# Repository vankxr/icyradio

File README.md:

# icyradio

A **S**oftware **D**efined **R**adio development board.

Initial project codename **Icy**radio originated from the device family name of the FPGA used in the [first version](https://github.com/vankxr/icyradio/tree/v1/qo100) (**ICE**40). Coincidently, the device family name of the FPGA used in this version (Artix) also resembles a very cold region, the Arctic, hence, the project codename still holds some of its sense :blush:.

## Main components
 - [XC7A100T-2FGG484](https://pt.mouser.com/datasheet/2/903/ds180_7Series_Overview-1591537.pdf) - FPGA
 - [Raspberry Pi CM4](https://datasheets.raspberrypi.com/cm4/cm4-datasheet.pdf) - Raspberry Pi Compute Module 4
 - [MT41K256M16TW-125](https://media-www.micron.com/-/media/client/global/documents/products/data-sheet/dram/ddr3/4gb_1_35v_ddr3l_xit_addendum.pdf?rev=993cd23ec9f2450c8cae38fcb35343bd) - DDR3 RAM
 - [AD9361](https://github.com/vankxr/icyradio/raw/v2/qo100/docs/ad9361_transceiver/AD9361_Datasheet_RevF.pdf) - Agile RF Transceiver
 - [SI5351C](https://www.silabs.com/documents/public/data-sheets/Si5351-B.pdf) - System clock synthesizer
 - [8V97003](https://www.renesas.com/us/en/document/dst/8v97003-datasheet?r=462341) - Frequency Synthesizer for external mixer support
 - [ADAU1372](https://www.analog.com/media/en/technical-documentation/data-sheets/ADAU1372.pdf) - Audio CODEC
 - [UPD301C](https://ww1.microchip.com/downloads/aemDocuments/documents/UNG/ProductDocuments/DataSheets/00003412A.pdf) - USB Power Delivery controller
 - [LT7182S](https://www.analog.com/media/en/technical-documentation/data-sheets/lt7182s.pdf) - Main Buck regulator

## Functional block diagram

#### v2
**Note: From v2 onwards, the only components in this repository are hardware related, no specific application software, like in v1 branches. Applications that use this hardware are kept in a separate repository (TODO: Add link)**
The goal of this project is to develop a flexible and feature rich SDR platform for tinkering. It will include, among other features, a mmWave synthesizer controlled by software to allow external mixers to be attached to the SDR and extend its frequency range (i.e. for 5G applications), and also allow interfacing to a Raspberry Pi Compute Module 4 for standalone operation.

## Dependencies
 - [vivado](https://www.xilinx.com/support/download.html) - FPGA toolchain
 - [arm-none-eabi-gcc](https://developer.arm.com/tools-and-software/open-source-software/developer-tools/gnu-toolchain/gnu-rm/downloads) - PD Controller MCU toolchain
 - [Device CMSIS](https://www.keil.com/dd2/) - CMSIS headers defining the MCU memories, peripherals, etc...
 - [Core CMSIS](https://github.com/ARM-software/CMSIS_5) - CMSIS headers defining the ARM Cores
 - [armmem](https://github.com/vankxr/armmem) - ELF file analyzer (required for the MCU Makefiles to work)
 - [SoapySDR](https://github.com/pothosware/SoapySDR) - Vendor and platform neutral SDR support library

## Software build instructions
TODO (In the meantime, check the github workflows)
### Kernel driver
TODO
### SoapySDR device driver
TODO

## Errata
 - The WP pin of the LT7182S regulator was left floating, with a placeholder resistor for pulling it up later, assuming it had an internal pulldown. Turns out it is floating, and thus it can be sampled internally as 1, write-protecting the device and forbidding configuration commands. A quick fix is to scrape a tiny bit of the ground plane near the WP resistor (R1120) pad, and shunting it to GND there with a blob of solder. The figure below exemplifies the process. The solder blob is marked in blue.

 - The FPGA INIT and DONE LED markings on the PCB are swapped (oops). In the picture below, it can be seen that D202 connects to the FPGA_DONE signal, yet it's labelled INIT. The FPGA_INIT signal connects to D201, and is labelled as DONE. It is merely an aesthetic problem, and does not affect functionality at all!

## Authors

* **João Silva** - [vankxr](https://github.com/vankxr)

## License

The content of this repository is licensed under the [GNU General Public License v3.0](LICENSE).

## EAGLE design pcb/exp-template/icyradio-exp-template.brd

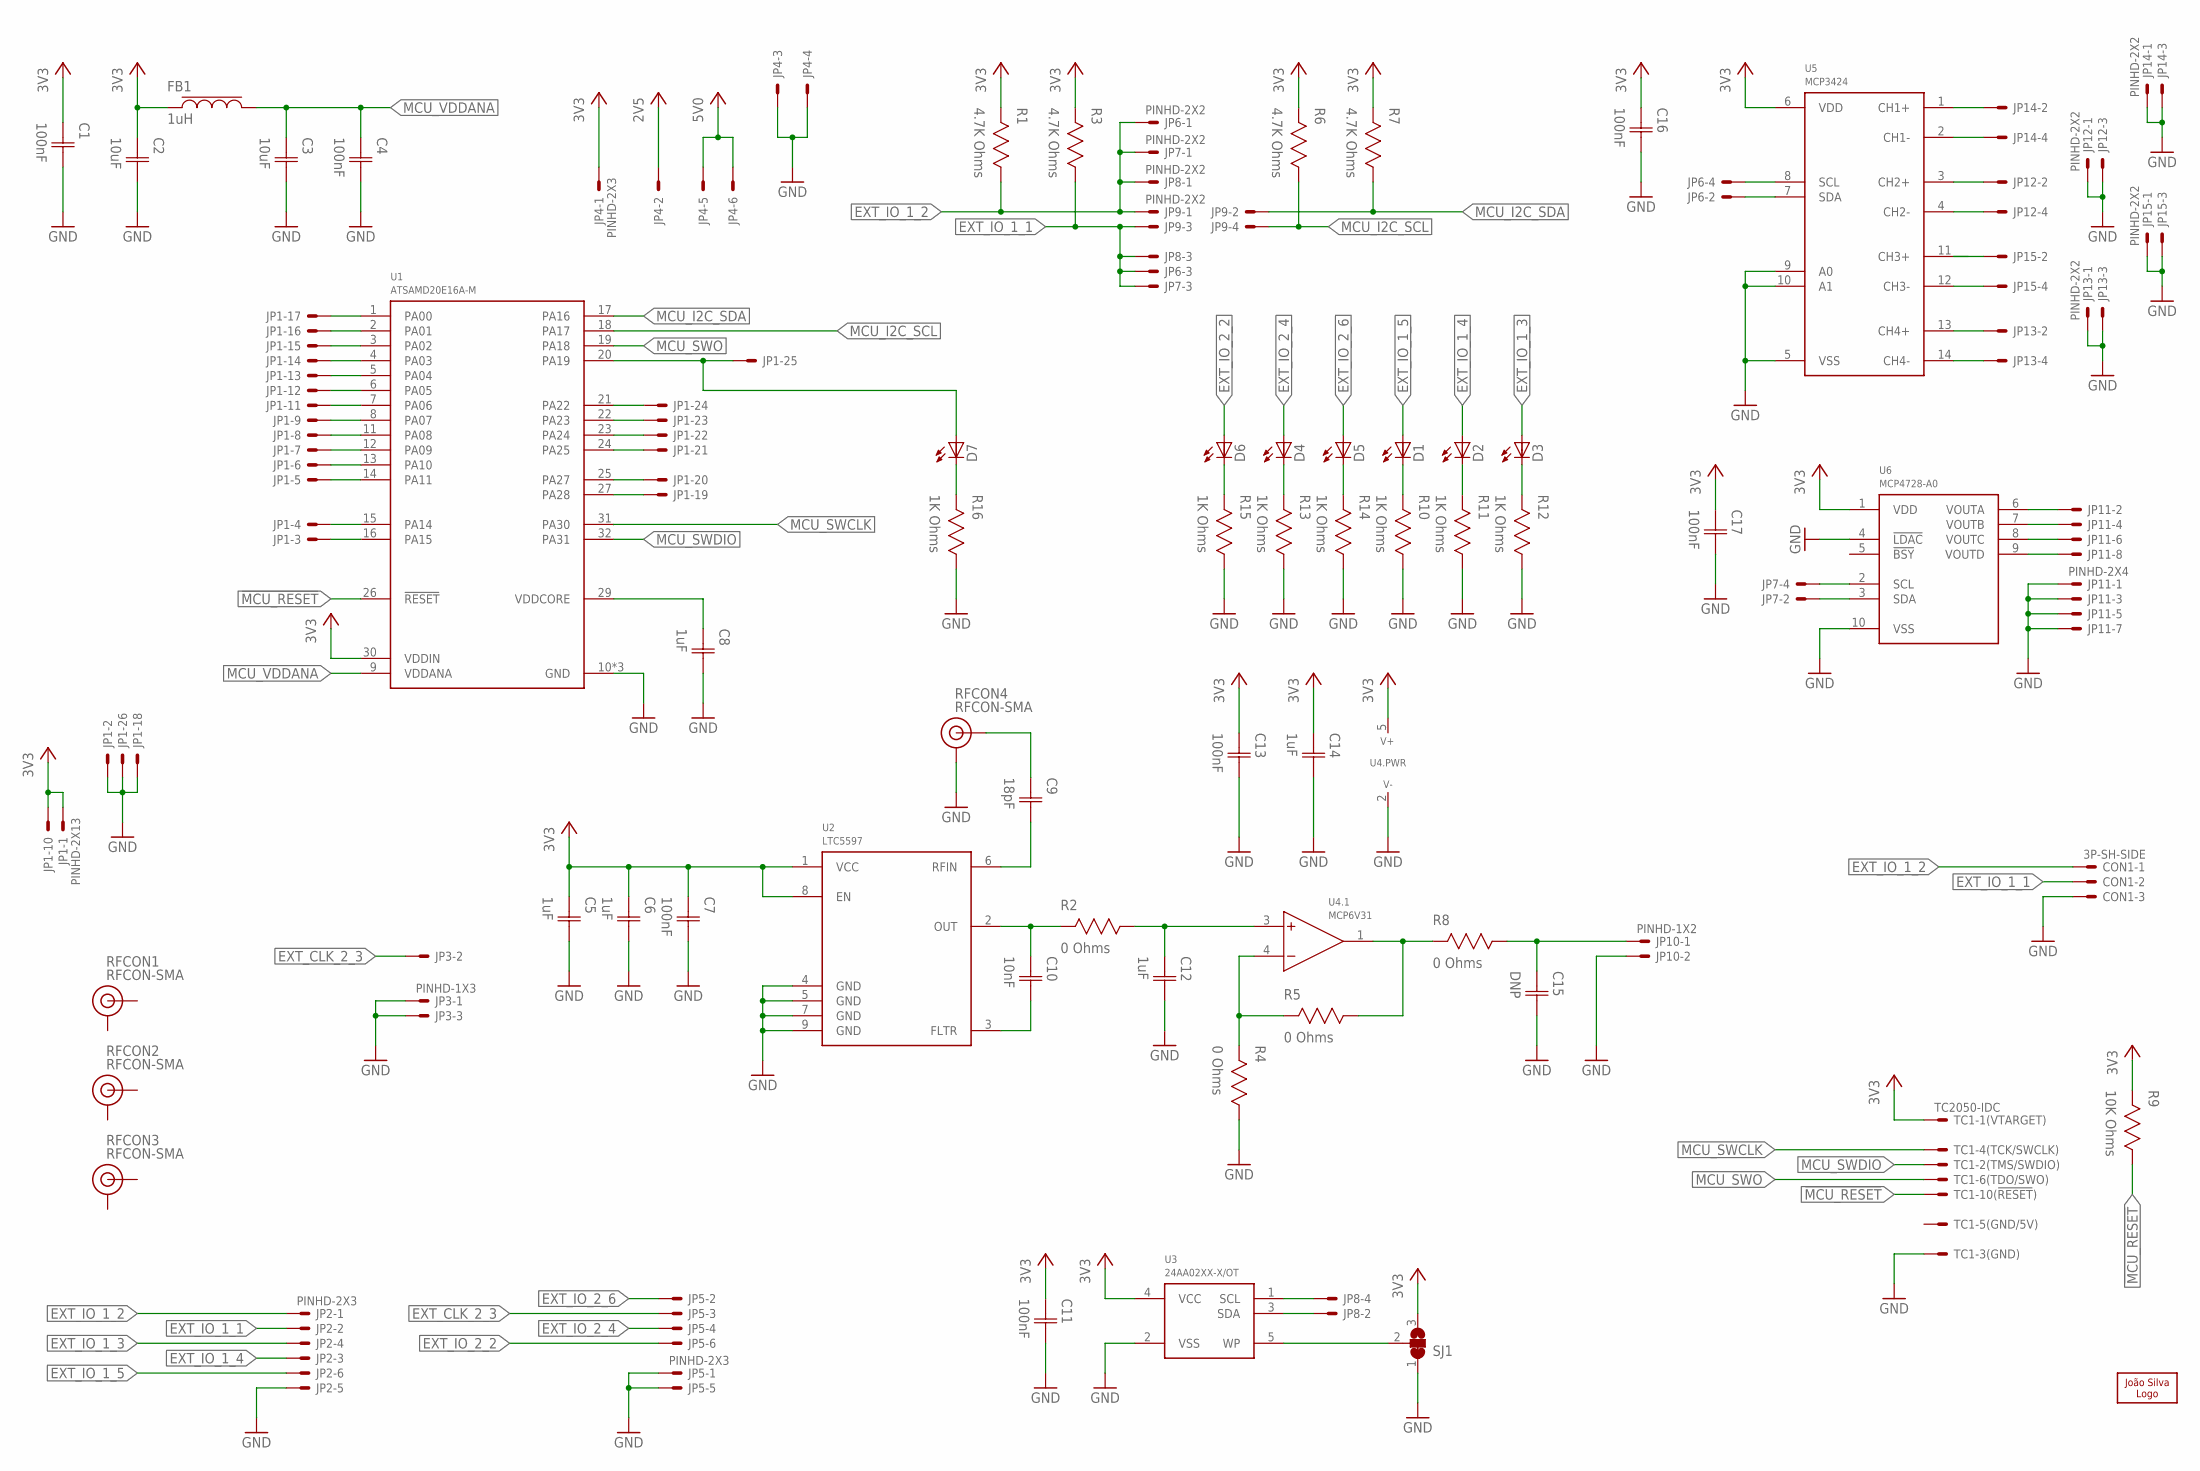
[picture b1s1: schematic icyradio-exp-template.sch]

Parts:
C1, C4, C7, C11, C13, C16, C17: 100nF; CAP0402
C2, C3: 10uF; CAP0402
C5, C6, C8, C12, C14: 1uF; CAP0402
C9: 18pF; CAP0402
C10: 10nF; CAP0402
C15: DNP; CAP0402
CON1: 3P-SH-SIDE; SH-03-SIDE
D1, D2, D3, D4, D5, D6, D7: LED0603; 0603
FB1: 1uH; IND0603
JP1: PINHD-2X13; 2X13
JP2, JP4, JP5: PINHD-2X3; 2X03
JP3: PINHD-1X3; 1X03
JP6, JP7, JP8, JP9, JP12, JP13, JP14, JP15: PINHD-2X2; 2X02
JP10: PINHD-1X2; 1X02
JP11: PINHD-2X4; 2X04
LOGO1: JSILVA-5MM; JSILVA_5MM
R1, R3, R6, R7: 4.7K Ohms; RES0402
R2, R4, R5, R8: 0 Ohms; RES0402
R9: 10K Ohms; RES0402
R10, R11, R12, R13, R14, R15, R16: 1K Ohms; RES0402
RFCON1, RFCON2, RFCON3, RFCON4: RFCON-SMA; SMA
SJ1: SJ2CS; SJ2C_S
TC1: TC2050-IDC
U1: ATSAMD20E16A-M; QFN32
U2: LTC5597; DFN8_2X2
U3: 24AA02XX-X/OT; SOT23-5
U4: MCP6V31; SOT23-5
U5: MCP3424; TSSOP14
U6: MCP4728-A0; MSOP10

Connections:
2V5: JP4.2
3V3: C1.1 (C1), C2.1 (C1), C5.1 (C1), C6.1 (C1), C7.1 (C1), C11.1 (C1), C13.1 (C1), C14.1 (C1), C16.1 (C1), C17.1 (C1), FB1.1, JP1.1, JP1.10, JP4.1, R1.2, R3.2, R6.2, R7.2, R9.2, SJ1.3, TC1.1, U1.30 (VDDIN), U2.1 (VCC), U2.8 (EN), U3.4 (VCC), U4.5 (V+), U5.6 (VDD), U6.1 (VDD)
5V0: JP4.5, JP4.6
!MCU_RESET: R9.1, TC1.10, U1.26 (!RESET)
ADC_C1_N: JP14.4, U5.2 (CH1-)
ADC_C1_P: JP14.2, U5.1 (CH1+)
ADC_C2_N: JP12.4, U5.4 (CH2-)
ADC_C2_P: JP12.2, U5.3 (CH2+)
ADC_C3_N: JP15.4, U5.12 (CH3-)
ADC_C3_P: JP15.2, U5.11 (CH3+)
ADC_C4_N: JP13.4, U5.14 (CH4-)
ADC_C4_P: JP13.2, U5.13 (CH4+)
ADC_I2C_SCL: JP6.4, U5.8 (SCL)
ADC_I2C_SDA: JP6.2, U5.7 (SDA)
DAC_I2C_SCL: JP7.4, U6.2 (SCL)
DAC_I2C_SDA: JP7.2, U6.3 (SDA)
DAC_VA: JP11.2, U6.6 (VOUTA)
DAC_VB: JP11.4, U6.7 (VOUTB)
DAC_VC: JP11.6, U6.8 (VOUTC)
DAC_VD: JP11.8, U6.9 (VOUTD)
EE_I2C_SCL: JP8.4, U3.1 (SCL)
EE_I2C_SDA: JP8.2, U3.3 (SDA)
EE_WP: SJ1.2, U3.5 (WP)
EXT_CLK_2_3: JP3.2, JP5.3
EXT_IO_1_1: CON1.2, JP2.2, JP6.3, JP7.3, JP8.3, JP9.3, R3.1
EXT_IO_1_2: CON1.1, JP2.1, JP6.1, JP7.1, JP8.1, JP9.1, R1.1
EXT_IO_1_3: D3.A, JP2.4
EXT_IO_1_4: D2.A, JP2.3
EXT_IO_1_5: D1.A, JP2.6
EXT_IO_2_2: D6.A, JP5.6
EXT_IO_2_4: D4.A, JP5.4
EXT_IO_2_6: D5.A, JP5.2
GND: C1.2 (C2), C2.2 (C2), C3.2 (C2), C4.2 (C2), C5.2 (C2), C6.2 (C2), C7.2 (C2), C8.2 (C2), C11.2 (C2), C12.2 (C2), C13.2 (C2), C14.2 (C2), C15.2 (C2), C16.2 (C2), C17.2 (C2), CON1.3, JP1.2, JP1.18, JP1.26, JP2.5, JP3.1, JP3.3, JP4.3, JP4.4, JP5.1, JP5.5, JP10.2, JP11.1, JP11.3, JP11.5, JP11.7, JP12.1, JP12.3, JP13.1, JP13.3, JP14.1, JP14.3, JP15.1, JP15.3, R4.1, R10.1, R11.1, R12.1, R13.1, R14.1, R15.1, R16.1, RFCON4.GND@0 (GND), RFCON4.GND@1 (GND), RFCON4.GND@2 (GND), RFCON4.GND@3 (GND), SJ1.1, TC1.3, U1.10 (GND), U1.28 (GND), U1.33 (GND), U2.4 (GND), U2.5 (GND), U2.7 (GND), U2.9 (GND), U3.2 (VSS), U4.2 (V-), U5.5 (VSS), U5.9 (A0), U5.10 (A1), U6.4 (!LDAC), U6.10 (VSS)
MCU_I2C_SCL: JP9.4, R6.1, U1.18 (PA17)
MCU_I2C_SDA: JP9.2, R7.1, U1.17 (PA16)
MCU_SWCLK: TC1.4, U1.31 (PA30)
MCU_SWDIO: TC1.2, U1.32 (PA31)
MCU_SWO: TC1.6, U1.19 (PA18)
MCU_VDDANA: C3.1 (C1), C4.1 (C1), FB1.2, U1.9 (VDDANA)
unnamed: C8.1 (C1), U1.29 (VDDCORE)
unnamed: D1.C, R10.2
unnamed: D2.C, R11.2
unnamed: D3.C, R12.2
unnamed: D4.C, R13.2
unnamed: D5.C, R14.2
unnamed: D6.C, R15.2
unnamed: D7.C, R16.2
unnamed: R5.1, R8.2, U4.1 (OUT)
unnamed: C10.2 (C2), U2.3 (FLTR)
unnamed: C10.1 (C1), R2.2, U2.2 (OUT)
unnamed: C12.1 (C1), R2.1, U4.3 (+IN)
unnamed: R4.2, R5.2, U4.4 (-IN)
unnamed: C9.1 (C1), RFCON4.SIGNAL
unnamed: C9.2 (C2), U2.6 (RFIN)
unnamed: C15.1 (C1), JP10.1, R8.1
P0: JP1.17, U1.1 (PA00)
P1: JP1.16, U1.2 (PA01)
P2: JP1.15, U1.3 (PA02)
P3: JP1.14, U1.4 (PA03)
P4: JP1.13, U1.5 (PA04)
P5: JP1.12, U1.6 (PA05)
P6: JP1.11, U1.7 (PA06)
P7: JP1.9, U1.8 (PA07)
P8: JP1.8, U1.11 (PA08)
P9: JP1.7, U1.12 (PA09)
P10: JP1.6, U1.13 (PA10)
P11: JP1.5, U1.14 (PA11)
P14: JP1.4, U1.15 (PA14)
P15: JP1.3, U1.16 (PA15)
P19: D7.A, JP1.25, U1.20 (PA19)
P22: JP1.24, U1.21 (PA22)
P23: JP1.23, U1.22 (PA23)
P24: JP1.22, U1.23 (PA24)
P25: JP1.21, U1.24 (PA25)
P27: JP1.20, U1.25 (PA27)
P28: JP1.19, U1.27 (PA28)

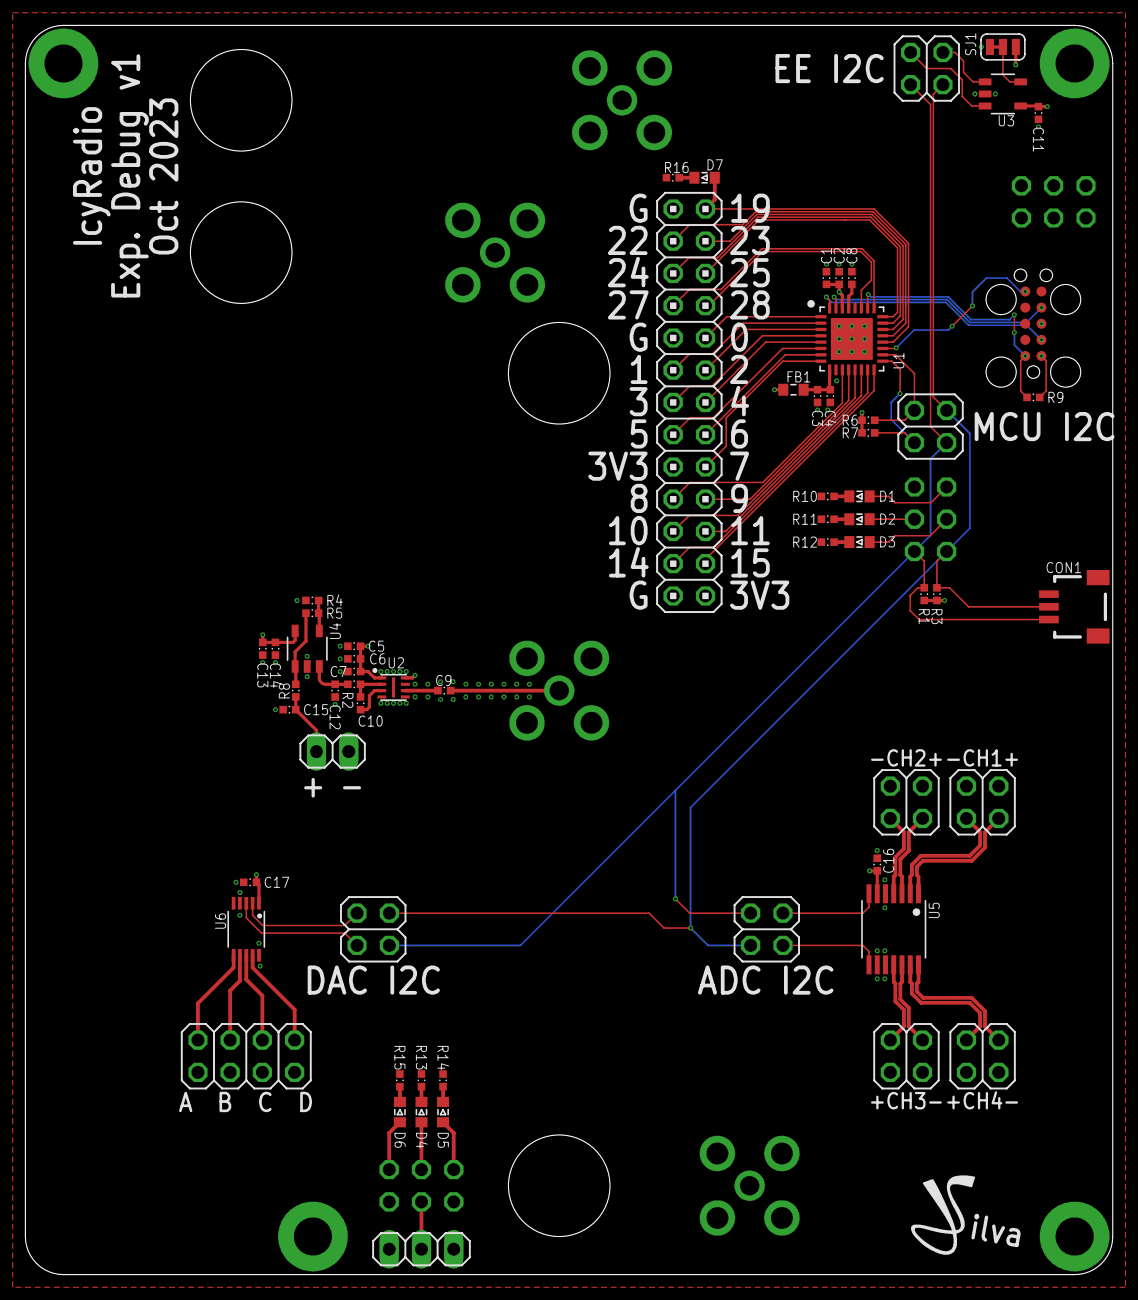
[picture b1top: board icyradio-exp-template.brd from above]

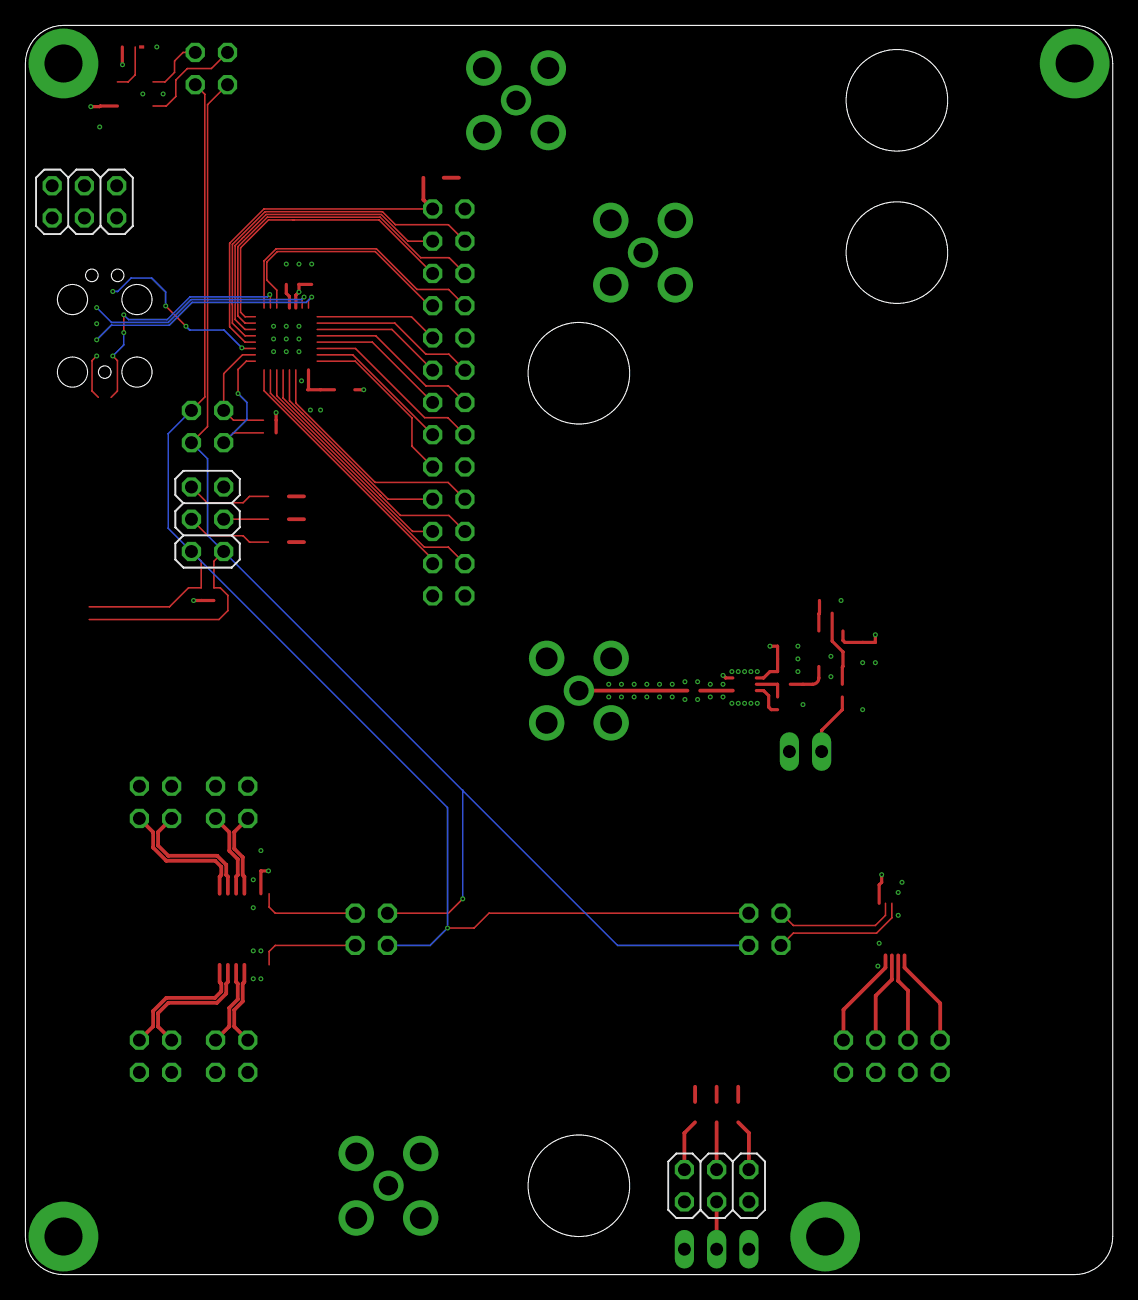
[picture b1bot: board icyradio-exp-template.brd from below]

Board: 4 copper layers, 85.7 x 98.4 mm, 70 parts (3 on the bottom side), 75 nets.

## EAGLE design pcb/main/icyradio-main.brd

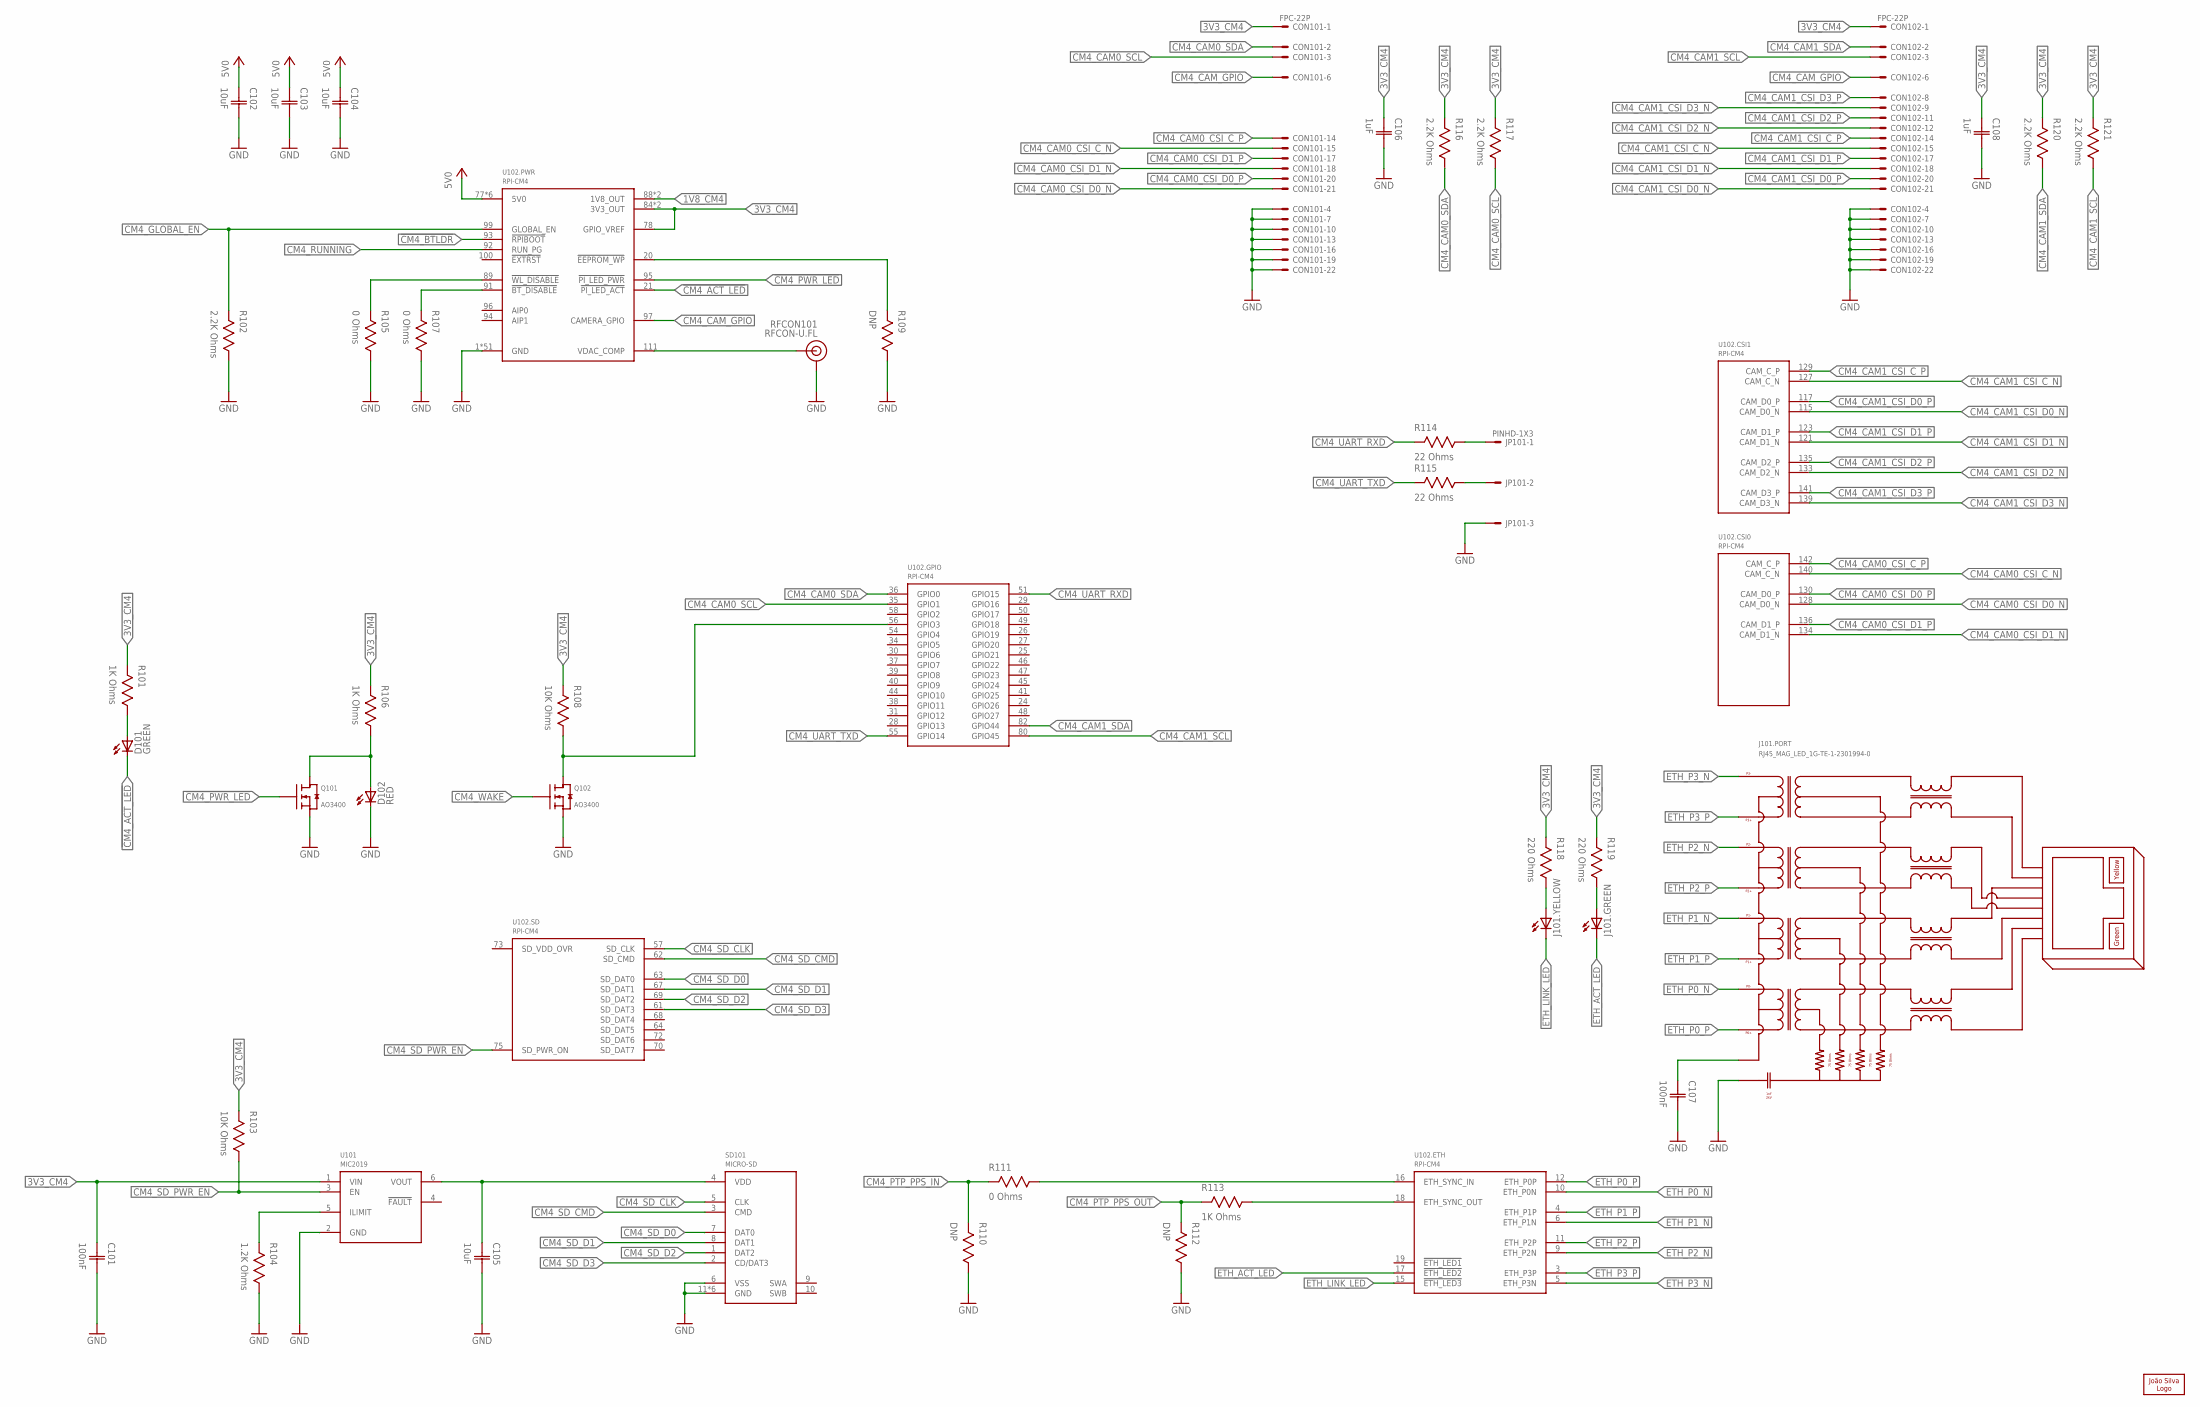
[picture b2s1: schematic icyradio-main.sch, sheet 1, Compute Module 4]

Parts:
C101, C107: 100nF; CAP0402
C102, C103, C104: 10uF; CAP0603
C105: 10uF; CAP0402
C106, C108: 1uF; CAP0402
CON101, CON102: FPC-22P
D101, D102: LED0603; 0603
J101: RJ45_MAG_LED_1G-TE-1-2301994-0; TE-1-2301994-0
JP101: PINHD-1X3; 1X03
LOGO101: JS-10MM; JS_10MM
Q101, Q102: AO3400; SOT23
R101, R106, R113: 1K Ohms; RES0402
R102, R116, R117, R120, R121: 2.2K Ohms; RES0402
R103, R108: 10K Ohms; RES0402
R104: 1.2K Ohms; RES0402
R105, R107, R111: 0 Ohms; RES0402
R109, R110, R112: DNP; RES0402
R114, R115: 22 Ohms; RES0402
R118, R119: 220 Ohms; RES0402
RFCON101: RFCON-U.FL; U.FL
SD101: MICRO-SD; TE-2201778-1
U101: MIC2019; SOT23-6
U102: RPI-CM4

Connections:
1V8_CM4: U102.88 (1V8_OUT), U102.90 (1V8_OUT)
3V3_CM4: C101.1 (C1), C106.1 (C1), C108.1 (C1), CON101.1, CON102.1, R101.2, R103.2, R106.2, R108.2, R116.2, R117.2, R118.2, R119.2, R120.2, R121.2, U101.1 (VIN), U102.78 (GPIO_VREF), U102.84 (3V3_OUT), U102.86 (3V3_OUT); also elsewhere on the board
3V3_CM4_SD: C105.1 (C1), SD101.4 (VDD), U101.6 (VOUT)
5V0: C102.1 (C1), C103.1 (C1), C104.1 (C1), U102.77 (5V0), U102.79 (5V0), U102.81 (5V0), U102.83 (5V0), U102.85 (5V0), U102.87 (5V0); also elsewhere on the board
!CM4_ACT_LED: D101.C, U102.21 (!PI_LED_ACT)
!CM4_BTLDR: U102.93 (!RPIBOOT); also elsewhere on the board
!CM4_BT_DIS: R107.2, U102.91 (!BT_DISABLE)
!CM4_EE_WP: R109.2, U102.20 (!EEPROM_WP)
!CM4_PWR_LED: Q101.1 (G), U102.95 (!PI_LED_PWR)
!CM4_WL_DIS: R105.2, U102.89 (!WL_DISABLE)
CM4_CAM0_CSI_C_N: CON101.15, U102.140 (CAM_C_N)
CM4_CAM0_CSI_C_P: CON101.14, U102.142 (CAM_C_P)
CM4_CAM0_CSI_D0_N: CON101.21, U102.128 (CAM_D0_N)
CM4_CAM0_CSI_D0_P: CON101.20, U102.130 (CAM_D0_P)
CM4_CAM0_CSI_D1_N: CON101.18, U102.134 (CAM_D1_N)
CM4_CAM0_CSI_D1_P: CON101.17, U102.136 (CAM_D1_P)
CM4_CAM0_SCL: CON101.3, R117.1, U102.35 (GPIO1)
CM4_CAM0_SDA: CON101.2, R116.1, U102.36 (GPIO0)
CM4_CAM1_CSI_C_N: CON102.15, U102.127 (CAM_C_N)
CM4_CAM1_CSI_C_P: CON102.14, U102.129 (CAM_C_P)
CM4_CAM1_CSI_D0_N: CON102.21, U102.115 (CAM_D0_N)
CM4_CAM1_CSI_D0_P: CON102.20, U102.117 (CAM_D0_P)
CM4_CAM1_CSI_D1_N: CON102.18, U102.121 (CAM_D1_N)
CM4_CAM1_CSI_D1_P: CON102.17, U102.123 (CAM_D1_P)
CM4_CAM1_CSI_D2_N: CON102.12, U102.133 (CAM_D2_N)
CM4_CAM1_CSI_D2_P: CON102.11, U102.135 (CAM_D2_P)
CM4_CAM1_CSI_D3_N: CON102.9, U102.139 (CAM_D3_N)
CM4_CAM1_CSI_D3_P: CON102.8, U102.141 (CAM_D3_P)
CM4_CAM1_SCL: CON102.3, R121.1, U102.80 (GPIO45)
CM4_CAM1_SDA: CON102.2, R120.1, U102.82 (GPIO44)
CM4_CAM_GPIO: CON101.6, CON102.6, U102.97 (CAMERA_GPIO)
CM4_CVBS: RFCON101.P$3 (SIGNAL), U102.111 (VDAC_COMP)
CM4_GLOBAL_EN: R102.2, U102.99 (GLOBAL_EN); also elsewhere on the board
CM4_GPIO3: Q102.3 (D), R108.1, U102.56 (GPIO3)
CM4_PTP_PPS_IN: R110.2, R111.2; also elsewhere on the board
CM4_PTP_PPS_OUT: R112.2, R113.2; also elsewhere on the board
CM4_RUNNING: U102.92 (RUN_PG); also elsewhere on the board
CM4_SD_CLK: SD101.5 (CLK), U102.57 (SD_CLK)
CM4_SD_CMD: SD101.3 (CMD), U102.62 (SD_CMD)
CM4_SD_D0: SD101.7 (DAT0), U102.63 (SD_DAT0)
CM4_SD_D1: SD101.8 (DAT1), U102.67 (SD_DAT1)
CM4_SD_D2: SD101.1 (DAT2), U102.69 (SD_DAT2)
CM4_SD_D3: SD101.2 (CD/DAT3), U102.61 (SD_DAT3)
CM4_SD_PWR_EN: R103.1, U101.3 (EN), U102.75 (SD_PWR_ON)
CM4_UART_RXD: R114.2, U102.51 (GPIO15)
CM4_UART_TXD: R115.2, U102.55 (GPIO14)
CM4_WAKE: Q102.1 (G); also elsewhere on the board
ETH_ACT_LED: J101.12 (C), U102.17 (!ETH_LED2)
ETH_LINK_LED: J101.14 (C), U102.15 (!ETH_LED3)
ETH_P0_N: J101.3 (P0-), U102.10 (ETH_P0N)
ETH_P0_P: J101.2 (P0+), U102.12 (ETH_P0P)
ETH_P1_N: J101.7 (P1-), U102.6 (ETH_P1N)
ETH_P1_P: J101.4 (P1+), U102.4 (ETH_P1P)
ETH_P2_N: J101.6 (P2-), U102.9 (ETH_P2N)
ETH_P2_P: J101.5 (P2+), U102.11 (ETH_P2P)
ETH_P3_N: J101.9 (P3-), U102.5 (ETH_P3N)
ETH_P3_P: J101.8 (P3+), U102.3 (ETH_P3P)
ETH_SYNC_IN: R111.1, U102.16 (ETH_SYNC_IN)
ETH_SYNC_OUT: R113.1, U102.18 (ETH_SYNC_OUT)
GND: C101.2 (C2), C102.2 (C2), C103.2 (C2), C104.2 (C2), C105.2 (C2), C106.2 (C2), C107.2 (C2), C108.2 (C2), CON101.4, CON101.7, CON101.10, CON101.13, CON101.16, CON101.19, CON101.22, CON102.4, CON102.7, CON102.10, CON102.13, CON102.16, CON102.19, CON102.22, D102.C, J101.10 (CHS_GND), J101.SHIELD@0 (CHS_GND), J101.SHIELD@1 (CHS_GND), JP101.3, Q101.2 (S), Q102.2 (S), R102.1, R104.1, R105.1, R107.1, R109.1, R110.1, R112.1, RFCON101.P$1 (GND), RFCON101.P$2 (GND), SD101.6 (VSS), SD101.11 (GND), SD101.12 (GND), SD101.13 (GND), SD101.14 (GND), SD101.15 (GND), SD101.16 (GND), U101.2 (GND), U102.1 (GND), U102.2 (GND), U102.7 (GND), U102.8 (GND), U102.13 (GND), U102.14 (GND), U102.22 (GND), U102.23 (GND), U102.32 (GND), U102.33 (GND), U102.42 (GND), U102.43 (GND), U102.52 (GND), U102.53 (GND), U102.59 (GND), U102.60 (GND), U102.65 (GND), U102.66 (GND), U102.71 (GND), U102.74 (GND), U102.98 (GND), U102.107 (GND), U102.108 (GND), U102.113 (GND), U102.114 (GND), U102.119 (GND), U102.120 (GND), U102.125 (GND), U102.126 (GND), U102.131 (GND), U102.132 (GND), U102.137 (GND), U102.138 (GND), U102.144 (GND), U102.150 (GND), U102.155 (GND), U102.156 (GND), U102.161 (GND), U102.162 (GND), U102.167 (GND), U102.168 (GND), U102.173 (GND), U102.174 (GND), U102.179 (GND), U102.180 (GND), U102.185 (GND), U102.186 (GND), U102.191 (GND), U102.192 (GND), U102.197 (GND), U102.198 (GND); also elsewhere on the board
unnamed: JP101.1, R114.1
unnamed: JP101.2, R115.1
unnamed: C107.1 (C1), J101.1 (CT)
unnamed: J101.11 (A), R119.1
unnamed: J101.13 (A), R118.1
unnamed: R104.2, U101.5 (ILIMIT)
unnamed: D101.A, R101.1
unnamed: D102.A, Q101.3 (D), R106.1
